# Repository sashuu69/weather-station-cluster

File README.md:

# Weather Station Cluster

## Introduction

The Weather Station Cluster is weather station system for ethusiasts that want to measure data for education and research purposes.

## Features

1. The device collects the following data:-
   1. Temperature
   2. Humidity
   3. Heat index
   4. Altitude
   5. Pressure
   6. Rain (in cm)
   7. Rain duration and strength
   8. Wind speed
   9. Wind direction
2. Collects the above mentioned parameters and stores the data to database.

## Folder Structure

1. code/arduino_mega-code: Contains code for Arduino Mega.
2. code/nodemcu-code: Contains code NodeMCU.
3. docs: PCB images (Top, Bottom and Drill).
4. eagle-design: Eagle design of PCB.
5. fusion360-design: STL files of rain guage, wind direction and wind speed.

## Library used

1. DHT22 Library - [GitHub](https://github.com/adafruit/DHT-sensor-library)
2. BMP280 Library - [GitHub](https://github.com/adafruit/Adafruit_BMP280_Library)
3. RTC Library - [GitHub](https://github.com/adafruit/RTClib)
4. ArduinoJSON Library - [GitHub](https://github.com/bblanchon/ArduinoJson)
5. Adafruit Sensor - [github.com](https://github.com/adafruit/Adafruit_Sensor)

## CAD Files

1. Rain sensor support - [Thingiverse](https://www.thingiverse.com/thing:4107951)

## Components Used

1. NodeMCU (x1) - [Tomson Electronics](https://www.tomsonelectronics.com/products/buy-node-mcu-esp-8266-with-cp-2102-online)
2. Micro SD card module (x1) - [Tomson Electronics](https://www.tomsonelectronics.com/products/micro-sd-card-module)
3. Arduino Mega (x1) - [Tomson Electronics](https://www.tomsonelectronics.com/products/buy-arduino-mega-2560-online-india)
4. DHT22 (x1) - [Tomson Electronics](https://www.tomsonelectronics.com/products/dht22-digital-temperature-and-humidity-sensor-module-am2302)
5. BMP 280 (x1) - [Tomson Electronics](https://www.tomsonelectronics.com/products/bmp-280-barometer-precision-atmospheric-pressure-sensor-module)
6. Rain sensor (x1) - [Tomson Electronics](https://www.tomsonelectronics.com/products/rain-drop-detection-sensor-rain-detector-weather-module)
7. Speed Measuring sensor Groove Coupler Module (x1) - [Tomson Electronics](https://www.tomsonelectronics.com/products/speed-measuring-sensor-groove-coupler-module-for-arduino)
8. RTC module (x1) - [Tomson Electronics](https://www.tomsonelectronics.com/products/ds1307-i2c-rtc-ds1307-24c32-real-time-clock-module)
9. Button cell (CR-2032) (x1) - [Tomson Electronics](https://www.tomsonelectronics.com/products/panasonic-cr-2032)
10. Female headers - [Robu (India)](https://robu.in/product/2mm-pitch-female-berg-strip-40x1-2pcs/)
11. Male header pins - [Robu (India)](https://robu.in/product/1x40-berg-strip-male-connector/)
12. DC Barrel Power Jack (x1) - [Tomson Electronics](https://www.tomsonelectronics.com/products/dc-barrel-power-jack)
13. LED (Red) (x4) - [Tomson Electronics](https://www.tomsonelectronics.com/products/led-basic-red-5mm-pack-of-10)
14. Diode IN 4007 (x1) - [Tomson Electronics](https://www.tomsonelectronics.com/products/diode-1n-4007)
15. 7805 5V regulator (x1) - [Amazon (India)](https://www.amazon.in/5-piece-voltage-regulator-7805/dp/0070530572)
16. LED (Green) (x3) - [Tomson Electronics](https://www.tomsonelectronics.com/products/led-basic-green-5-mm)
17. Micro SD Card Module (x1) - [Tomson Electronics](https://www.tomsonelectronics.com/products/micro-sd-card-module)
18. Rain drop detection sensor Module (x1) - [Tomson Electronics](https://www.tomsonelectronics.com/products/rain-drop-detection-sensor-rain-detector-weather-module)
19. Resistor (10K Ohms) (x2) - [Tomson Electronics](https://www.tomsonelectronics.com/products/1ko-12ko-carbon-film-resistor)
20. Resistor (220 Ohms) (x7) - [Tomson Electronics](https://www.tomsonelectronics.com/products/100k-ohm-metal-film-resistor?variant=8737726038107)
21. Neodymium disc magnets (4x1.5mm) (x2) - [Tomson Electronics](https://www.tomsonelectronics.com/products/neodymium-disc-magnets?variant=37753432768707)
22. Neodymium disc magnets (4x1.5mm) (x1) - [Tomson Electronics](https://www.tomsonelectronics.com/products/neodymium-disc-magnets?variant=37753432801475)
23. PLA (1KG) (WHITE) (x1) - [Tomson Electronics](https://www.augment3di.com/product/white-pla-premium-filament-1kg/)
24. Pole, Wires, tapes and zip ties

## PCB design

### Info Board

#### Top View

#### Bottom View

#### Drill View

### Process Board

#### Top View

#### Bottom View

#### Drill View

## Pre-Installation Steps

1. Connect the sensors as per circuit diagram.
2. Flash the NodeMCU code.
3. Connect to NodeMCU WiFi hotspot (SSID: Home Weather Station Mini) WiFi hotspot.
4. Goto http://192.168.4.1 (NodeMCU gateway).
5. Enter WiFi credentials.
6. After connecting to WiFi, use Fing to get IP address of NodeMCU.
7. Goto http://ip-address and enter username (admin) and password (pasword).
8. Enter server IP address, API key and other necessary details.

## Sensor Info

| Sensor name      | Features                                       |
| ---------------- | ---------------------------------------------- |
| DHT22            | Temperature, Humidity and Heat Index           |
| BMP280           | Temperature, atmospheric pressure and altitude |
| Rain Guage       | Rain in CM                                     |
| Rain drop sensor | Rain Duration and Strength                     |
| Annemometer      | Wind speed and wind direction                  |

## Contributions

1. Sashwat K (@sashuu6) <hi@sashwat.in>
2. Tharun P Karun (@tharunpkarun) <tpk@tharun.me>
3. Sreeram (STL files) [YouTube](https://www.youtube.com/channel/UC3x_svxO5Dxl0VesjEMpuGg)

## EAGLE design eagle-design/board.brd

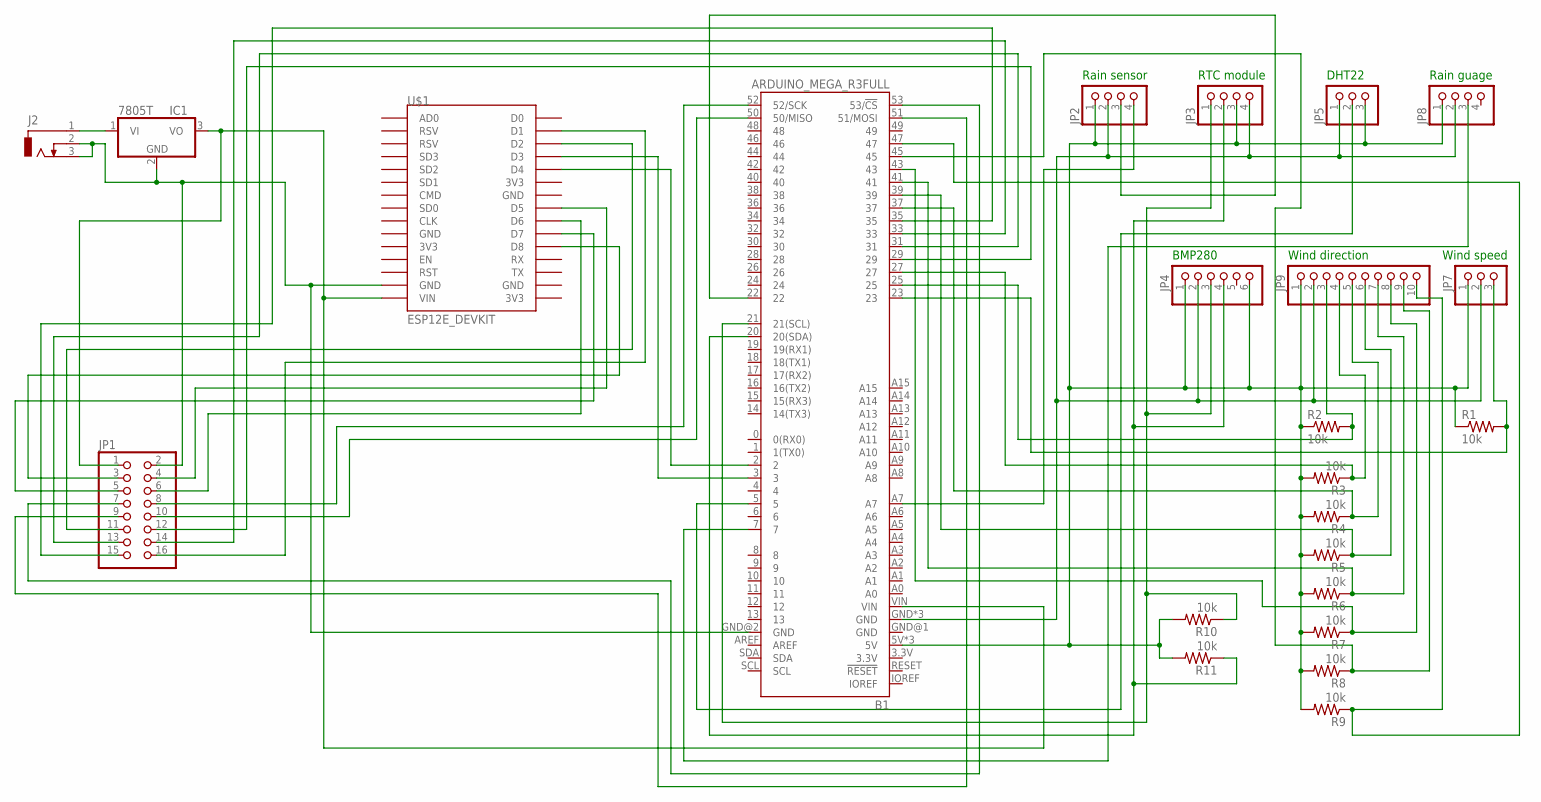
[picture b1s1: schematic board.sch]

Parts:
B1: ARDUINO_MEGA_R3FULL; ARDUINO_MEGA_NO_SILK
IC1: 7805T; TO220H
J2: DCJ0303
JP1: PINHD-2X8/90; 2X08/90
JP2, JP3, JP8: PINHD-1X4; 1X04
JP4: PINHD-1X6; 1X06
JP5, JP7: PINHD-1X3; 1X03
JP9: PINHD-1X10; 1X10
R1, R2, R3, R4, R5, R6, R7, R8, R9, R10, R11: 10k; 0207/10
U$1: ESP12E_DEVKIT

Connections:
unnamed: IC1.1 (VI), J2.1
unnamed: B1.GND@2 (GND), IC1.2 (GND), J2.2, J2.3, JP1.2, U$1.GND@1 (GND)
unnamed: B1.5V, B1.5V@1 (5V), B1.5V@2 (5V), JP2.1, JP3.3, JP4.1, JP4.6, JP5.3, JP7.1, JP8.1, JP9.1, R1.1, R2.1, R3.2, R4.2, R5.2, R6.2, R7.2, R8.2, R9.2, R10.2, R11.2
unnamed: B1.VIN, IC1.3 (VO), JP1.1, U$1.VIN
unnamed: B1.23, JP7.3, R1.2
unnamed: B1.GND, B1.GND@3 (GND), B1.GND@4 (GND), JP2.2, JP3.4, JP4.2, JP5.1, JP7.2, JP8.2, JP9.2
unnamed: B1.A7, JP2.4
unnamed: B1.2, U$1.D4
unnamed: B1.5, JP5.2
unnamed: B1.7, JP8.3
unnamed: B1.33, JP1.14
unnamed: B1.3, U$1.D3
unnamed: JP1.11, U$1.D2
unnamed: B1.29, JP1.12
unnamed: B1.31, JP1.13
unnamed: B1.35, JP1.15
unnamed: JP1.16, U$1.D1
unnamed: JP1.6, U$1.D6
unnamed: JP1.3, U$1.D8
unnamed: JP1.4, U$1.D5
unnamed: B1.53 (53/!CS), JP1.7
unnamed: JP1.5, U$1.D7
unnamed: B1.52 (52/SCK), JP1.8
unnamed: B1.51 (51/MOSI), JP1.9
unnamed: B1.25, JP9.3, R2.2
unnamed: B1.50 (50/MISO), JP1.10
unnamed: B1.27, JP9.4, R3.1
unnamed: B1.37, JP9.5, R4.1
unnamed: B1.39, JP9.6, R5.1
unnamed: B1.41, JP9.7, R6.1
unnamed: B1.43, JP9.8, R7.1
unnamed: B1.45, JP9.9, R8.1
unnamed: B1.47, JP9.10, R9.1
unnamed: B1.22, JP2.3
unnamed: B1.21 (21(SCL)), JP3.1, JP4.3, R10.1
unnamed: B1.20 (20(SDA)), JP3.2, JP4.4, R11.1

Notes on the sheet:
Rain sensor
RTC module
DHT22
BMP280
Wind direction
Wind speed
Rain guage

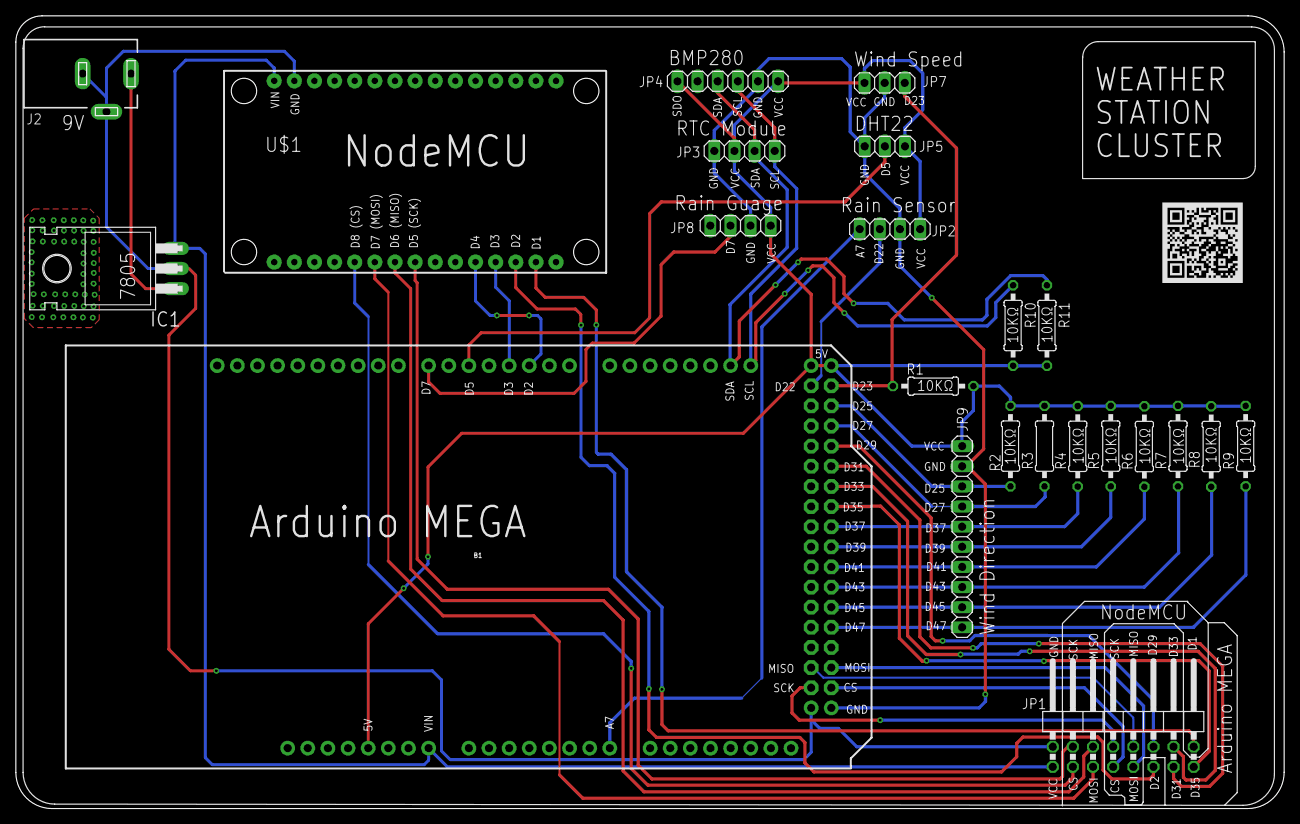
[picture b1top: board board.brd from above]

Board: 2 copper layers, 160.0 x 100.0 mm, 23 parts (0 on the bottom side), 36 nets.

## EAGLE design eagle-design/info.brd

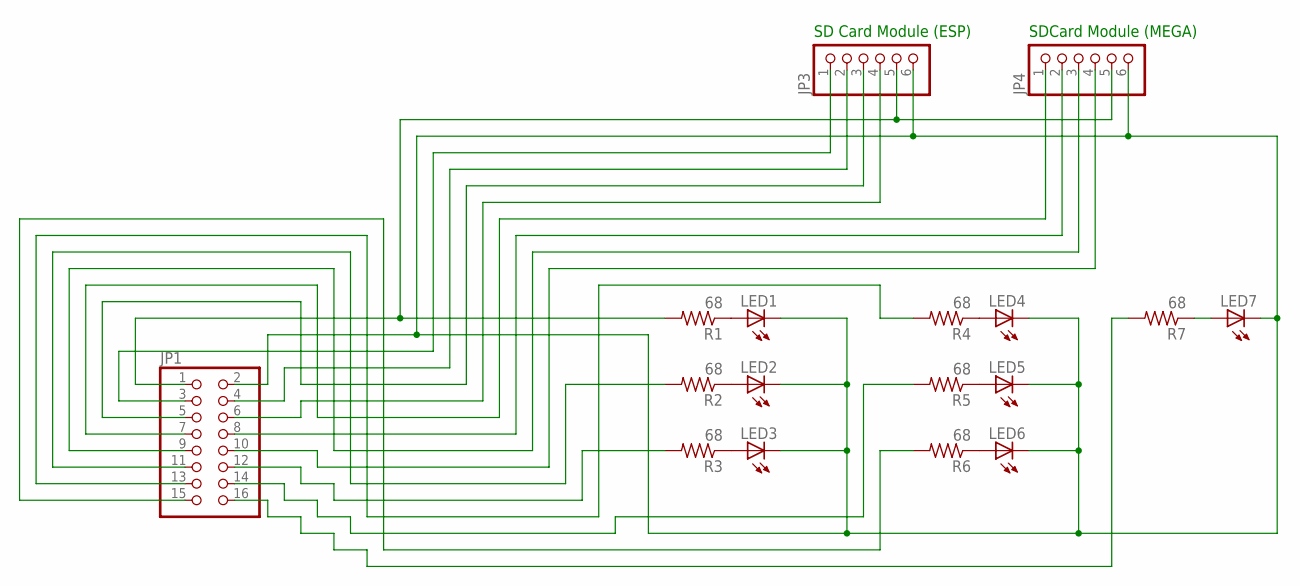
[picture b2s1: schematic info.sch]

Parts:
JP1: PINHD-2X8/90; 2X08/90
JP3, JP4: PINHD-1X6; 1X06
LED1, LED2, LED3, LED4, LED5, LED6, LED7: LED3MM
R1, R2, R3, R4, R5, R6, R7: 68; 0204/7

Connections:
unnamed: LED4.A, R4.1
unnamed: LED5.A, R5.1
unnamed: LED6.A, R6.1
unnamed: LED7.A, R7.1
unnamed: LED1.A, R1.1
unnamed: LED2.A, R2.1
unnamed: LED3.A, R3.1
unnamed: JP1.10, JP4.4
unnamed: JP1.2, JP3.6, JP4.6, LED1.K (C), LED2.K (C), LED3.K (C), LED4.K (C), LED5.K (C), LED6.K (C), LED7.K (C)
unnamed: JP1.11, R2.2
unnamed: JP1.1, JP3.5, JP4.5, R1.2
unnamed: JP1.3, JP3.1
unnamed: JP1.4, JP3.2
unnamed: JP1.5, JP3.3
unnamed: JP1.6, JP3.4
unnamed: JP1.7, JP4.1
unnamed: JP1.8, JP4.2
unnamed: JP1.9, JP4.3
unnamed: JP1.12, R3.2
unnamed: JP1.13, R4.2
unnamed: JP1.14, R5.2
unnamed: JP1.15, R6.2
unnamed: JP1.16, R7.2

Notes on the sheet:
SD Card Module (ESP)
SDCard Module (MEGA)

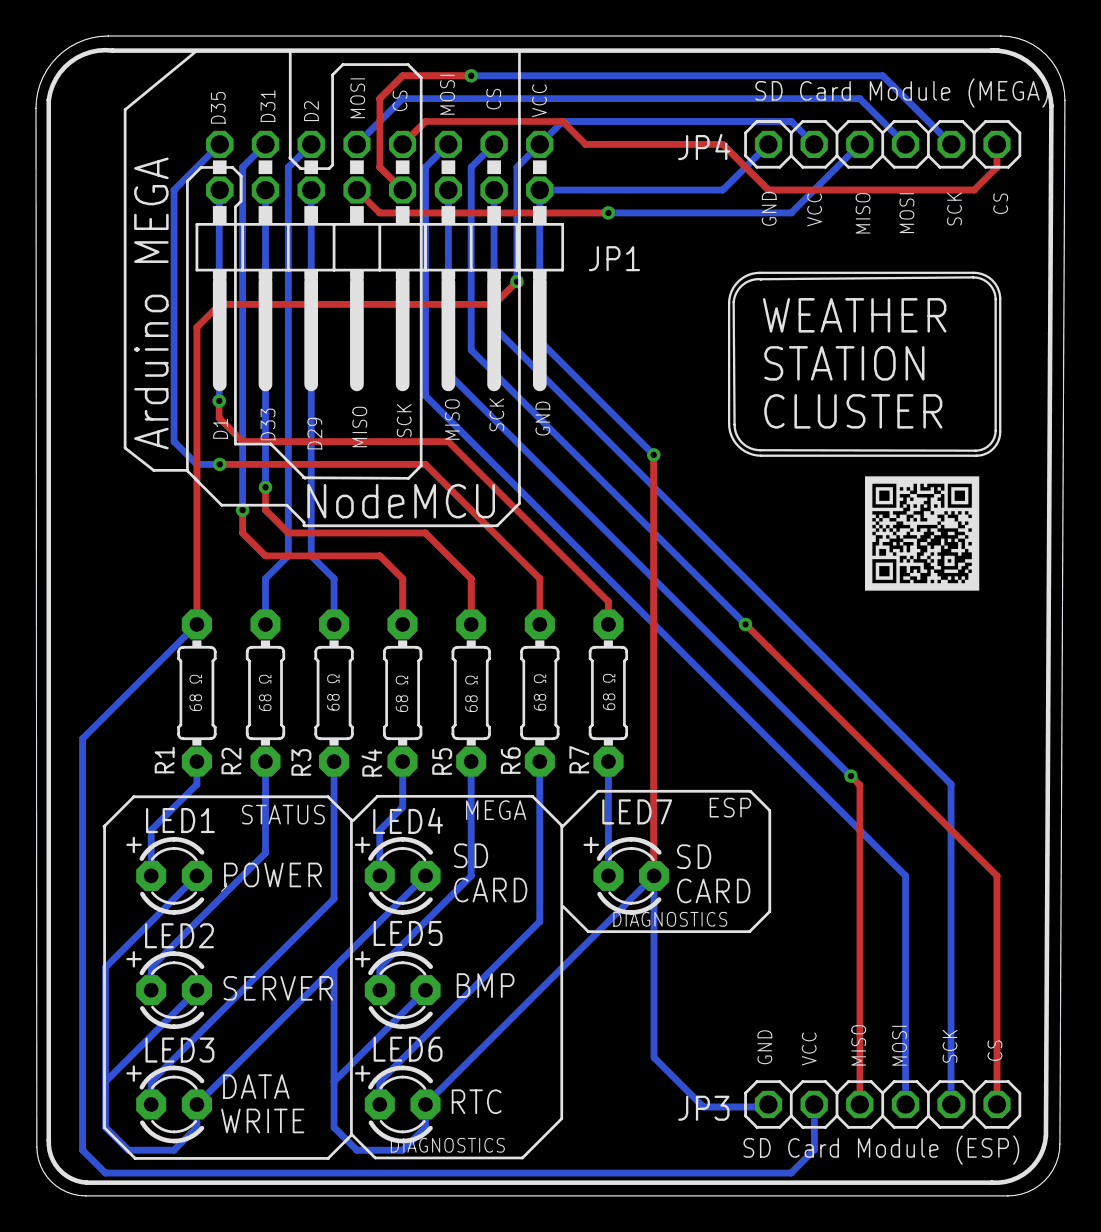
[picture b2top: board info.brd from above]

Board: 2 copper layers, 57.2 x 64.4 mm, 17 parts (0 on the bottom side), 23 nets.

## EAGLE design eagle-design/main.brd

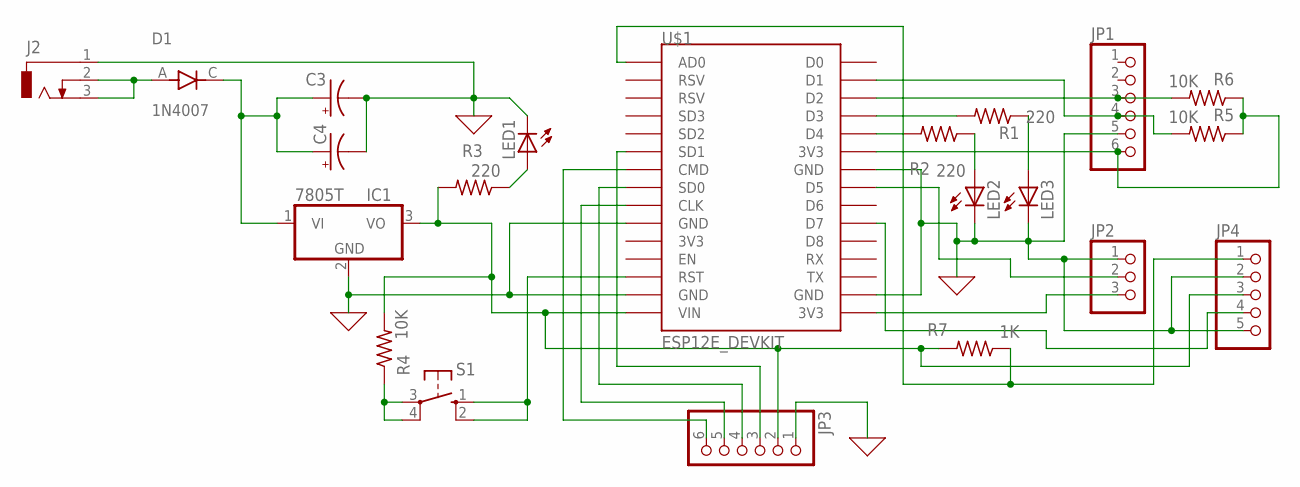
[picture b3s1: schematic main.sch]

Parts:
C3, C4: CPOL-USE2,5-6E; E2,5-6E
D1: 1N4007; DIOAD1060W80L520D270
IC1: 7805T; TO220H
J2: DCJ0303
JP1, JP3: PINHD-1X6; 1X06
JP2: PINHD-1X3; 1X03
JP4: PINHD-1X55X2MM; 1_05X2MM
LED1, LED2, LED3: LED3MM
R1, R2, R3: 220; 0805-THM
R4, R5, R6: 10K; 0805-THM
R7: 1K; 0805-THM
S1: 10-XX; B3F-10XX
U$1: ESP12E_DEVKIT

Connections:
0: C3.-, C4.-, IC1.2 (GND), J2.1, JP1.5, JP2.1, JP3.1, JP4.2, JP4.5, LED1.K (C), LED2.K (C), LED3.K (C), U$1.GND@0 (GND), U$1.GND@1 (GND), U$1.GND@2 (GND), U$1.GND@3 (GND)
unnamed: D1.A, J2.2, J2.3
unnamed: LED1.A, R3.1
unnamed: LED2.A, R2.1
unnamed: LED3.A, R1.1
unnamed: R1.2, U$1.D3
unnamed: R2.2, U$1.D4
unnamed: JP1.3, R6.2, U$1.D2
unnamed: JP1.4, R5.2, U$1.D1
unnamed: JP2.3, U$1.3V3@2 (3V3)
unnamed: S1.1 (S), S1.2 (S1), U$1.RST
unnamed: JP2.2, U$1.D5
unnamed: R4.1, S1.3, S1.4 (P1)
unnamed: JP1.6, R5.1, R6.1, U$1.3V3@1 (3V3)
unnamed: IC1.3 (VO), JP3.2, JP4.3, R3.2, R4.2, R7.2, U$1.VIN
unnamed: JP4.1, R7.1, U$1.AD0
unnamed: JP4.4, U$1.D7
unnamed: JP3.4, U$1.SD0
unnamed: C3.+, C4.+, D1.C, IC1.1 (VI)
unnamed: JP3.3, U$1.SD1
unnamed: JP3.5, U$1.CLK
unnamed: JP3.6, U$1.CMD

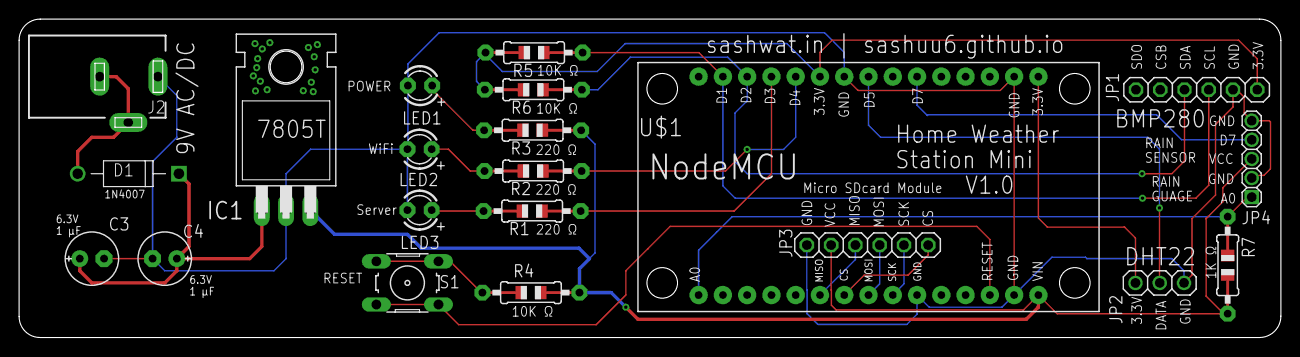
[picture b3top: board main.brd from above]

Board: 2 copper layers, 132.1 x 33.3 mm, 21 parts (0 on the bottom side), 22 nets.

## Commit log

2020-10-09 Added base documentation
2020-11-19 Added eagle design
2020-11-19 Added new code
2020-11-19 Added updated eagle design
2020-11-19 Added .gitignore
2020-11-19 Added new design and export image
2020-11-19 Basic esp code complete
2020-11-19 Updated docs
2020-11-21 Working on HTML template
2020-11-21 Dashboard almost complete
2020-11-21 EPROM complete
2020-11-21 Added 404 rank support
2020-11-22 Added OTA support
2020-11-26 Added support for reed switch and rain sensor
2020-11-26 Updated PCB export images
2020-11-27 Micro SD Card reader added to eagle design ; New export images added
2020-11-30 Added BMP library
2020-12-02 Updated documentation
2020-12-03 Added debug code
2020-12-04 Added CAD files
2020-12-04 Added datacenter docker compose
2020-12-04 Working on frontend
2020-12-04 added change
2020-12-05 Intermediate code
2020-12-05 completed datacenter code
2020-12-05 Completed datacenter docker compose code
2020-12-05 Added frontend docker-compose
2020-12-06 Under work
2020-12-11 Changed structure; moved from mongodb,mysql -> postgres
2020-12-13 Latest changes
2020-12-13 Added schema for datacenter
2020-12-13 Added new backup
2020-12-13 Added nano code
2020-12-13 Added debug code for arduino nano
2020-12-13 Completed arduino nano code
2020-12-14 Updated libraries
2020-12-14 Made some changes
2020-12-20 nano code redesign
2020-12-20 Testing
2020-12-27 working on debug nano code
2020-12-27 made some structural changes
2020-12-27 Removed cad designs and arduino libraries
2020-12-27 Fixed doc errors
2020-12-27 Added STL file links for rain guage and rain sensor support
2020-12-27 Updated component list
2020-12-28 Debug code complete. Calibrarion complete.
2021-01-26 Updated Mega Code
2021-01-26 Renamed file names
2021-01-26 Removed debug code
2021-01-26 home-weather-station-mini -> weather-station-cluster = 1
2021-01-26 home-weather-station-mini -> weather-station-cluster = 2
2021-01-26 Made changes to code
2021-01-29 Added new code for arduino mega
2021-01-30 ewmoved eagle.epf
2021-01-30 Added new eagle design and docs export
2021-02-05 Added pcb design
2021-02-06 Addedd new design
2021-02-07 Added motherboard design and image exports
2021-02-07 Updated READE.md
2021-02-13 Added new design
2021-02-13 exported board designs
2021-02-13 New updates
2021-02-14 Added wind direction sensor stl files
2021-02-14 Added rain guage stl files
2021-02-14 Updated document files
2021-02-21 Added support for Arduino mega
2021-02-21 Added support for wind speed and wind direction
2021-02-23 Updated eagle design
2021-02-23 Updated PCB exports
2021-02-23 Fixed serial communication pin arduino mega
2021-02-25 Added eagle save file
2021-02-25 Updated eagle data
2021-02-26 Fixed RTC bug
2021-03-02 Updated data
2021-03-02 Updated board design
    Increased track width
2021-03-02 new PCB exports
    info board
2021-03-02 Updated bugs
2021-03-02 small changes
2021-03-02 Updated board design
2021-03-02 Exported new board designs
2021-03-09 for temp purpose
2021-03-09 Updated code
2021-03-09 Added support for wind direction
2021-06-13 Added design image and updated readme

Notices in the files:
parts and their libraries:
SparkFun-Boards: Licensing: Creative Commons ShareAlike 4.0 International - https://creativecommons.org/licenses/by-sa/4.0
